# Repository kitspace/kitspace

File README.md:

> ❗ Archived, new development here: [kitspace-v2](https://github.com/kitspace/kitspace-v2)

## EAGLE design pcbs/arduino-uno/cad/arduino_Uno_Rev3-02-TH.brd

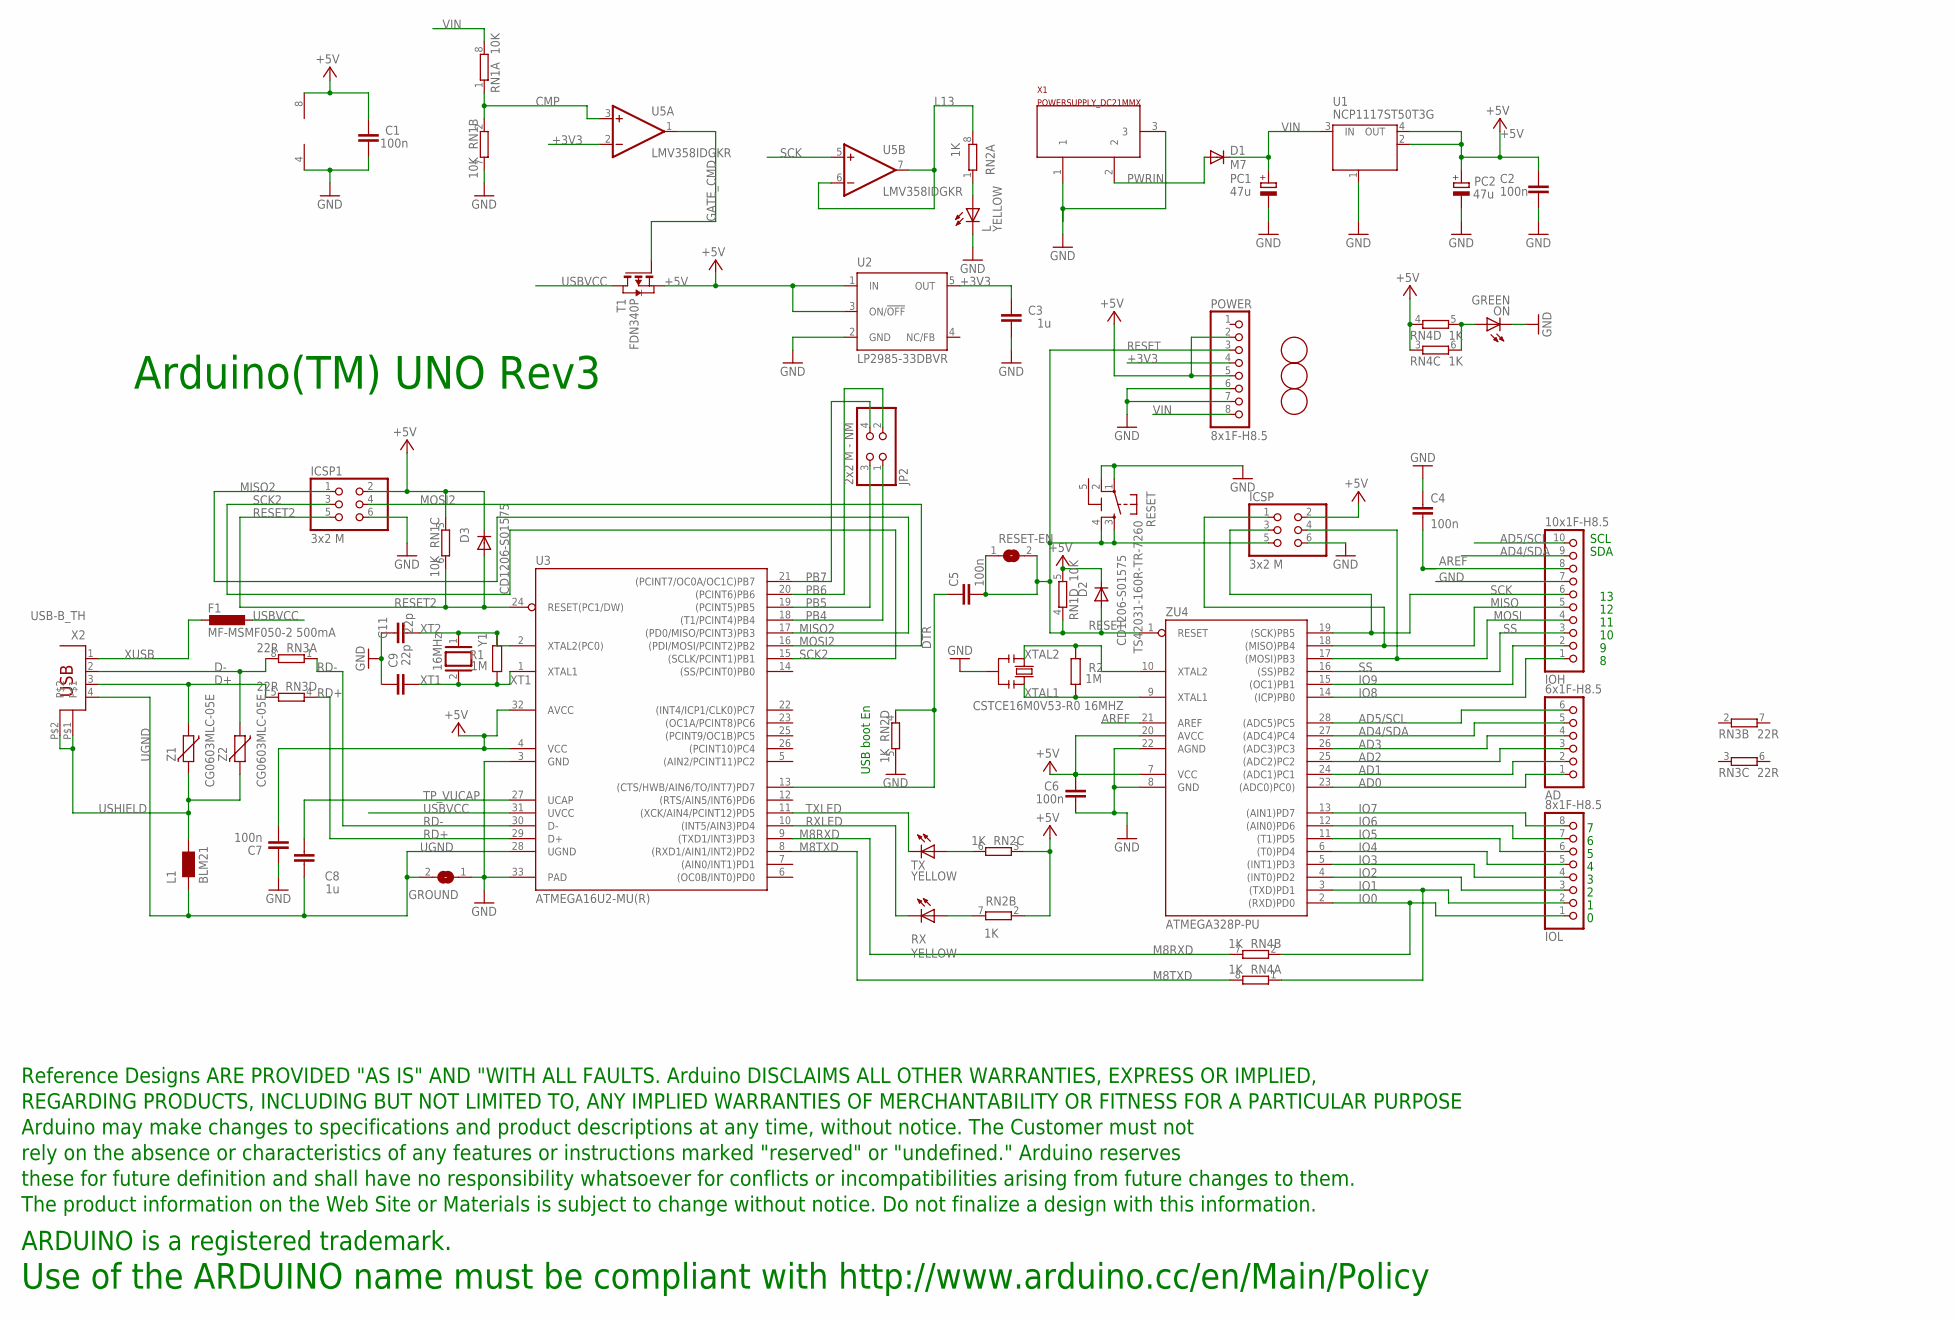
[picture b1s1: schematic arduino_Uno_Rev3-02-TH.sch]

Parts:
AD: 6x1F-H8.5; 1X06
C1, C2, C4, C5, C6, C7: 100n; C0603-ROUND
C3, C8: 1u; C0603-ROUND
C9, C11: 22p; C0603-ROUND
D1: M7; SMB
D2, D3: CD1206-S01575; MINIMELF
F1: MF-MSMF050-2 500mA; L1812
FD1, FD2, FD3: FIDUCIALMOUNT; FIDUCIA-MOUNT
GROUND: SJ
ICSP, ICSP1: 3x2 M; 2X03
IOH: 10x1F-H8.5; 1X10
IOL: 8x1F-H8.5; 1X08
JP2: 2x2 M - NM; 2X02
L: YELLOW; CHIP-LED0805
L1: BLM21; 0805
ON: GREEN; CHIP-LED0805
PC1, PC2: 47u; PANASONIC_D
POWER: 8x1F-H8.5; 1X08
R1, R2: 1M; R0603-ROUND
RESET: TS42031-160R-TR-7260; TS42
RESET-EN: SJ
RN1: 10K; CAY16
RN2, RN4: 1K; CAY16
RN3: 22R; CAY16
RX: YELLOW; CHIP-LED0805
T1: FDN340P; SOT-23
TX: YELLOW; CHIP-LED0805
U1: NCP1117ST50T3G; SOT223
U2: LP2985-33DBVR; SOT23-DBV
U3: ATMEGA16U2-MU(R); MLF32
U5: LMV358IDGKR; MSOP08
U$1: DISCLAIMER
X1: POWERSUPPLY_DC21MMX; POWERSUPPLY_DC-21MM
X2: USB-B_TH; PN61729
Y1: 16MHz; QS
Y2: CSTCE16M0V53-R0 16MHZ; RESONATOR
Z1, Z2: CG0603MLC-05E; CT/CN0603
ZU4: ATMEGA328P-PU; DIL28-3

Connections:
5-GND: RESET.5 (5-GND)
+3V3: C3.2, POWER.4, U2.5 (OUT), U5.2 (-IN)
+5V: C1.2, C2.2, C6.2, C7.1, D2.C, D3.C, ICSP.2, ICSP1.2, PC2.+, POWER.2, POWER.5, RN1.3 (1), RN1.5 (2), RN2.2 (1), RN2.3 (1), RN4.3 (1), RN4.4 (1), T1.2 (S), U1.2 (OUT), U1.4 (OUT), U2.1 (IN), U2.3 (ON/!OFF), U3.4 (VCC), U3.32 (AVCC), U5.8 (V+), ZU4.7 (VCC), ZU4.20 (AVCC)
AD0: AD.1, ZU4.23 ((ADC0)PC0))
AD1: AD.2, ZU4.24 ((ADC1)PC1)
AD2: AD.3, ZU4.25 ((ADC2)PC2)
AD3: AD.4, ZU4.26 ((ADC3)PC3)
AD4/SDA: AD.5, IOH.9, ZU4.27 ((ADC4)PC4)
AD5/SCL: AD.6, IOH.10, ZU4.28 ((ADC5)PC5)
AREF: C4.2, IOH.8, ZU4.21 (AREF)
CMP: RN1.1, RN1.2 (1), U5.3 (+IN)
D+: RN3.5 (2), X2.3, Z1.1
D-: RN3.8 (2), X2.2, Z2.1
DTR: C5.1, RN2.4 (1), U3.13 ((CTS/HWB/AIN6/TO/INT7)PD7)
GATE_CMD: T1.3 (G), U5.1 (OUT)
GND: C1.1, C2.1, C3.1, C4.1, C6.1, C7.2, C9.2, C11.2, GROUND.1, ICSP.6, ICSP1.6, IOH.7, L.C, ON.C, PC1.-, PC2.-, POWER.6, POWER.7, RESET.1, RESET.2, RN1.7 (2), RN2.5 (2), U1.1 (GND/ADJ), U2.2 (GND), U3.3 (GND), U3.33 (PAD), U5.4 (V-), X1.1, X1.3, Y2.2, ZU4.8 (GND), ZU4.22 (AGND)
IO0: IOL.1, RN4.2 (1), ZU4.2 ((RXD)PD0)
IO1: IOL.2, RN4.1, ZU4.3 ((TXD)PD1)
IO2: IOL.3, ZU4.4 ((INT0)PD2)
IO3: IOL.4, ZU4.5 ((INT1)PD3)
IO4: IOL.5, ZU4.6 ((T0)PD4)
IO5: IOL.6, ZU4.11 ((T1)PD5)
IO6: IOL.7, ZU4.12 ((AIN0)PD6)
IO7: IOL.8, ZU4.13 ((AIN1)PD7)
IO8: IOH.1, ZU4.14 ((ICP)PB0)
IO9: IOH.2, ZU4.15 ((OC1)PB1)
L13: RN2.8 (2), U5.6 (-IN), U5.7 (OUT)
M8RXD: RN4.7 (2), U3.9 ((TXD1/INT3)PD3)
M8TXD: RN4.8 (2), U3.8 ((RXD1/AIN1/INT2)PD2)
MISO: ICSP.1, IOH.5, ZU4.18 ((MISO)PB4)
MISO2: ICSP1.1, U3.17 ((PD0/MISO/PCINT3)PB3)
MOSI: ICSP.4, IOH.4, ZU4.17 ((MOSI)PB3)
MOSI2: ICSP1.4, U3.16 ((PDI/MOSI/PCINT2)PB2)
unnamed: L.A, RN2.1
unnamed: ON.A, RN4.5 (2), RN4.6 (2)
unnamed: RN2.7 (2), RX.A
unnamed: RN2.6 (2), TX.A
PB4: JP2.1, U3.18 ((T1/PCINT4)PB4)
PB5: JP2.3, U3.19 ((PCINT5)PB5)
PB6: JP2.2, U3.20 ((PCINT6)PB6)
PB7: JP2.4, U3.21 ((PCINT7/OC0A/OC1C)PB7)
PWRIN: D1.A, X1.2
RD+: RN3.4 (1), U3.29 (D+)
RD-: RN3.1, U3.30 (D-)
RESET: C5.2, D2.A, ICSP.5, POWER.3, RESET.3, RESET.4, RESET-EN.1, RESET-EN.2, RN1.4 (1), ZU4.1 (RESET)
RESET2: D3.A, ICSP1.5, RN1.6 (2), U3.24 (RESET(PC1/DW))
RXLED: RX.C, U3.10 ((INT5/AIN3)PD4)
SCK: ICSP.3, IOH.6, U5.5 (+IN), ZU4.19 ((SCK)PB5)
SCK2: ICSP1.3, U3.15 ((SCLK/PCINT1)PB1)
SS: IOH.3, ZU4.16 ((SS)PB2)
TP_VUCAP: C8.1, U3.27 (UCAP)
TXLED: TX.C, U3.11 ((XCK/AIN4/PCINT12)PD5)
UGND: C8.2, GROUND.2, L1.1, U3.28 (UGND), X2.4
USBVCC: F1.1, T1.1 (D), U3.31 (UVCC)
USHIELD: L1.2, X2.P$1, X2.P$2, Z1.2, Z2.2
VIN: D1.C, PC1.+, POWER.8, RN1.8 (2), U1.3 (IN)
XT1: C9.1, R1.1, U3.1 (XTAL1), Y1.2
XT2: C11.1, R1.2, U3.2 (XTAL2(PC0)), Y1.1
XTAL1: R2.1, Y2.3, ZU4.9 (XTAL1)
XTAL2: R2.2, Y2.1, ZU4.10 (XTAL2)
XUSB: F1.2, X2.1

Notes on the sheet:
Arduino(TM) UNO Rev3
USB boot En
SDA
SCL
Use of the ARDUINO name must be compliant with http://www.arduino.cc/en/Main/Policy

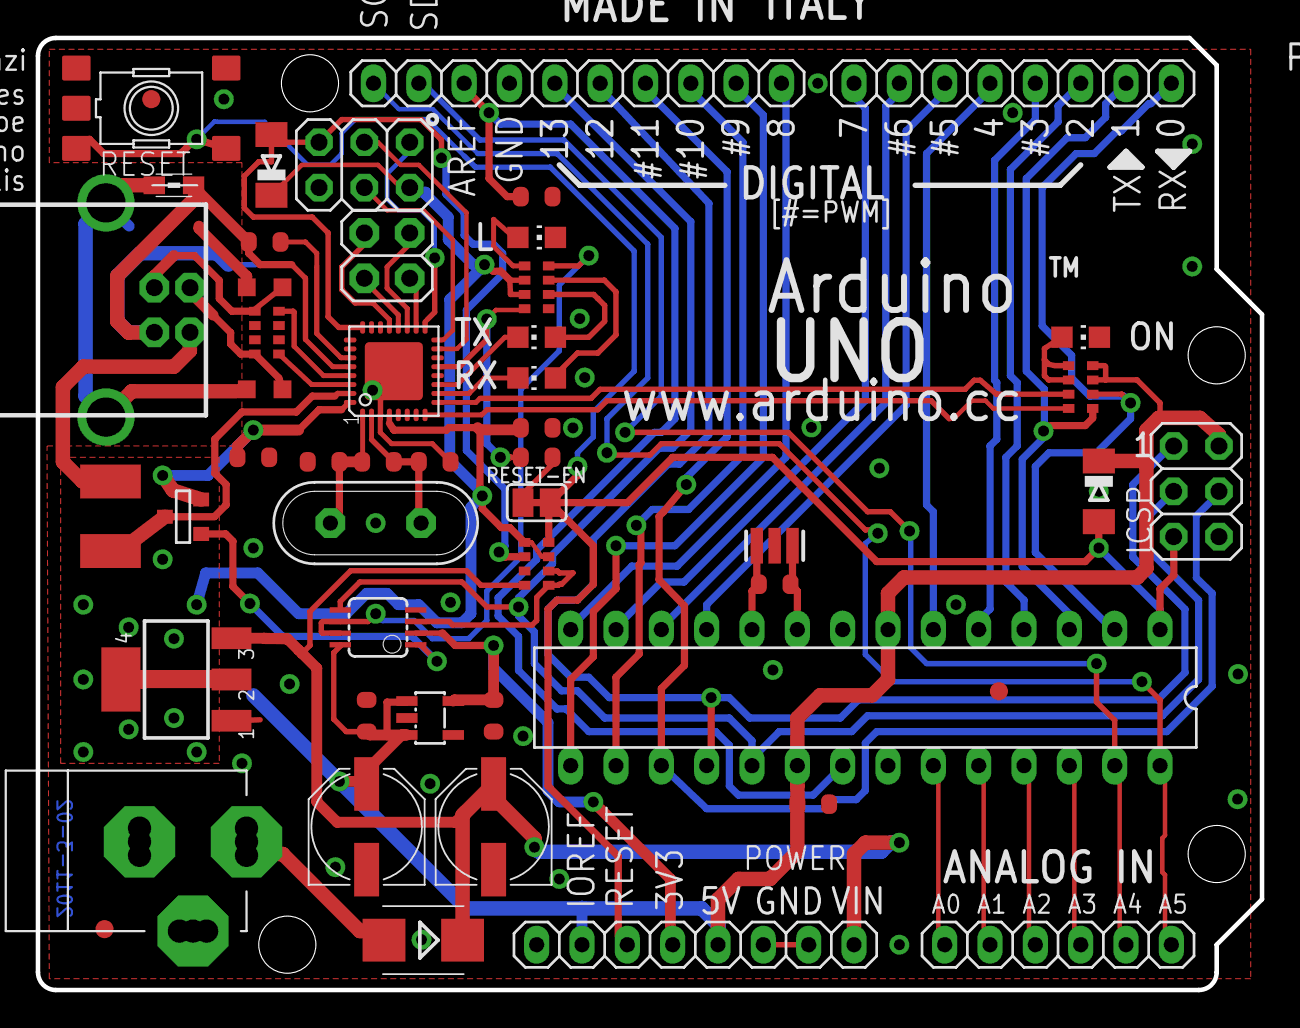
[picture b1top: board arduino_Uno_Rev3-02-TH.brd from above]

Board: 2 copper layers, 68.6 x 53.3 mm, 53 parts (1 on the bottom side), 60 nets.

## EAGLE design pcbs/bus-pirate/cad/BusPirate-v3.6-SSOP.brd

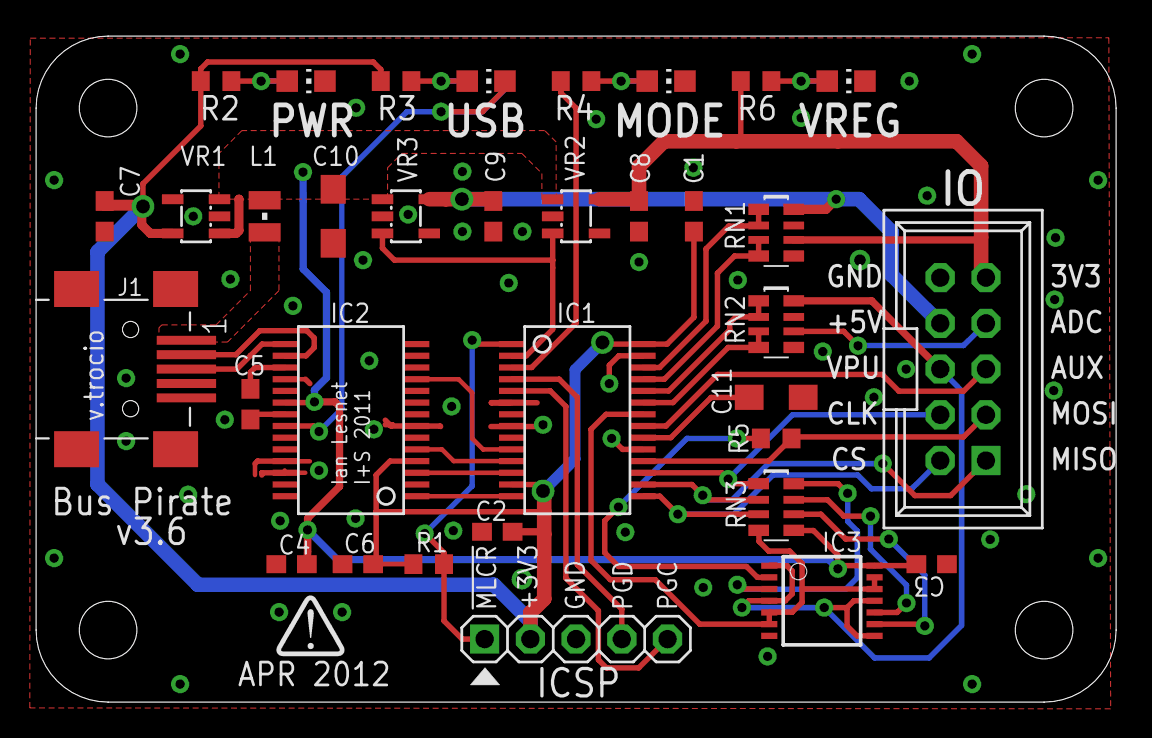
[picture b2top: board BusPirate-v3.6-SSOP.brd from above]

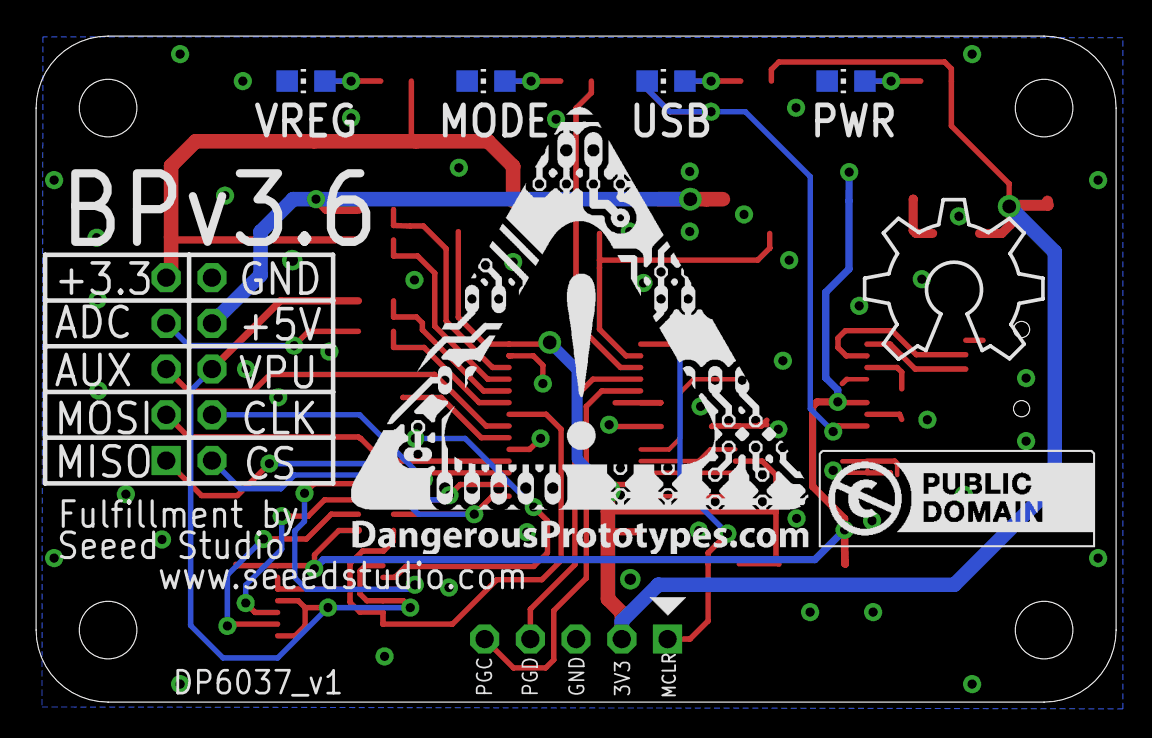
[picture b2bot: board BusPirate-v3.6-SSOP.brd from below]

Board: 2 copper layers, 60.0 x 37.0 mm, 43 parts (7 on the bottom side), 40 nets.

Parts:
C1, C2, C3, C4, C5, C6: 0.1uF; C603
C7, C8, C9: 1uF; C603
C10, C11: 10uF; SMC_A
IC1: PIC24FJ64GA002; SSOP28
IC2: FT232RL; SSOP28
IC3: 4066; TSSOP14
ICSP: 1X05
IO: HEADER2X5-SHRD-PTH-B; PINSHRD_PTH_2X05B
J1: CON-USB-MINI-BUSB1; CONN_USB_MINI-B
L1: 700mA+ ferrite; WE-KI_0805_B
LED1, LED1A, LED2, LED2A, LED3, LED3A, LED4, LED4A: CHIP-LED0805
LOGO1: LOGO_CC-0
PCB1: PCB_DP_RECTANGLE-37X60; DP6037_V1
R1, R5: 2K; R603
R2, R3, R4, R6: 1K1; R603
RN1, RN2, RN3: 10k; RN8P-4R-CRA06S
U$1: DP-LOGO
U$2: OSHW_8X350_NOTEXT
U$3: DP_LOGO_ART_1X1
VR1, VR2: MCP1801T-3302I/OT; SOT-23-5
VR3: MCP1801T-5002I/OT; SOT-23-5

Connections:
$N26: J1.VUSB, L1.2
ADC: IO.7, RN2.6
ADC1: IC1.23, RN2.3, RN2.4
ADC2: IC1.24, RN2.1, RN2.2
ADC3: IC1.25, RN1.3, RN1.4
ADC4: IC1.26, RN1.1, RN1.2
AUX1: IC1.21, IO.5
CLK: IC1.17, IO.4, RN3.1
CS: IC1.15, IO.2, RN3.3
CTS: IC1.10, IC2.11
GND: C1.2, C2.2, C3.2, C4.2, C5.2, C6.2, C7.2, C8.2, C9.2, C10.-, C11.-, IC1.6, IC1.7, IC1.8, IC1.19, IC1.27, IC2.7, IC2.18, IC2.21, IC2.25, IC2.26, IC3.7, ICSP.3, IO.10, J1.GND, LED1.C, LED1A.C, LED2.C, LED2A.C, LED3.C, LED3A.C, RN1.5, RN1.7, RN2.5, RN2.7, VR1.2, VR2.2, VR3.2
LD1: IC1.3, R4.2
MCLR: IC1.1, ICSP.1, R1.1
MISO: IC1.16, IO.1, RN3.2
MOSI: IC1.18, IO.3, R5.1
unnamed: IC3.2, R5.2
unnamed: IC3.9, RN3.6
unnamed: C11.+, IC1.20
unnamed: IC3.10, RN3.7
unnamed: IC3.3, RN3.8
unnamed: LED2.A, LED2A.A, R4.1
unnamed: LED1.A, LED1A.A, R2.1
unnamed: C5.1, IC2.17
unnamed: LED4.A, LED4A.A, R3.1
unnamed: IC2.15, J1.D+
unnamed: IC2.16, J1.D-
unnamed: LED3.A, LED3A.A, R6.1
PGC: IC1.5, ICSP.5
PGD: IC1.4, ICSP.4
PULLUPEN: IC1.22, IC3.5, IC3.6, IC3.12, IC3.13, RN3.4
RTS: IC1.12, IC2.3
RX: IC1.11, IC2.5
RXLED: IC2.22, LED4.C, LED4A.C
SWV33: C8.1, IO.9, R6.2, RN1.6, VR2.5
SWV50: C9.1, IO.8, RN1.8, VR3.5
TX: IC1.14, IC2.1
V+: C3.1, C4.1, C10.+, IC2.20, IC3.14, L1.1, RN3.5, VR1.1, VR1.3, VR2.1, VR3.1
VCC: C1.1, C2.1, C6.1, C7.1, IC1.13, IC1.28, IC2.4, ICSP.2, R1.2, R2.2, R3.2, VR1.5
VEXTERN: IC3.1, IC3.4, IC3.8, IC3.11, IO.6, RN2.8
VREGEN: IC1.2, VR2.3, VR3.3

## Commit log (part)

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2021-03-04 Add re-direct for turn signal
2021-03-09 Bump elliptic from 6.5.2 to 6.5.4
    Bumps [elliptic](https://github.com/indutny/elliptic) from 6.5.2 to 6.5.4.
    - [Release notes](https://github.com/indutny/elliptic/releases)
    - [Commits](https://github.com/indutny/elliptic/compare/v6.5.2...v6.5.4)
2021-03-10 Add odour stimulator board (#322)
2021-03-11 Upgrade tracespace tools to ^4.2
2021-03-11 Work around updated whats-that-gerber matching more files
2021-03-12 Make /submit work with updated tracespace
2021-03-12 Add global plausible for custom events
2021-03-12 Add plausible events for extension install
2021-03-12 Omit ibom for maulwurf
2021-03-13 Try aux click handler for aisler
2021-03-15 Remove check for plausible function
2021-03-17 Simplify order PCB tracking
2021-03-17 Add s to Order PCBs event
2021-03-18 Add tinyogx project
2021-03-22 Add openflexure-constant-current-illumination
2021-03-24 Remove smoke test
2021-03-30 Bump y18n from 3.2.1 to 3.2.2
    Bumps [y18n](https://github.com/yargs/y18n) from 3.2.1 to 3.2.2.
    - [Release notes](https://github.com/yargs/y18n/releases)
    - [Changelog](https://github.com/yargs/y18n/blob/master/CHANGELOG.md)
    - [Commits](https://github.com/yargs/y18n/commits)
2021-04-14 Add boards from the beehive project (#329)
2021-04-18 feat: Updates board URL to source repository
    Pull request to merge kitspace code has been merged see https://github.com/drspangle/infidel-sensor/pull/23
2021-04-19 Change beehive url to beehive-org
2021-04-22 Make sure kicad plotting folders for multi are seperate
2021-04-25 Bump ini from 1.3.5 to 1.3.8 (#325)
    Bumps [ini](https://github.com/isaacs/ini) from 1.3.5 to 1.3.8.
    - [Release notes](https://github.com/isaacs/ini/releases)
    - [Commits](https://github.com/isaacs/ini/compare/v1.3.5...v1.3.8)
2021-04-26 Bump http-proxy from 1.18.0 to 1.18.1 (#303)
    Bumps [http-proxy](https://github.com/http-party/node-http-proxy) from 1.18.0 to 1.18.1.
    - [Release notes](https://github.com/http-party/node-http-proxy/releases)
    - [Changelog](https://github.com/http-party/node-http-proxy/blob/master/CHANGELOG.md)
    - [Commits](https://github.com/http-party/node-http-proxy/compare/1.18.0...1.18.1)
2021-05-01 fix: Corrects repo typo
2021-05-05 Added 3 Channel Diversity System Controller (#335)
2021-05-06 Bump ua-parser-js from 0.7.21 to 0.7.28
    Bumps [ua-parser-js](https://github.com/faisalman/ua-parser-js) from 0.7.21 to 0.7.28.
    - [Release notes](https://github.com/faisalman/ua-parser-js/releases)
    - [Commits](https://github.com/faisalman/ua-parser-js/compare/0.7.21...0.7.28)
2021-05-10 Bump hosted-git-info from 2.8.5 to 2.8.9
    Bumps [hosted-git-info](https://github.com/npm/hosted-git-info) from 2.8.5 to 2.8.9.
    - [Release notes](https://github.com/npm/hosted-git-info/releases)
    - [Changelog](https://github.com/npm/hosted-git-info/blob/v2.8.9/CHANGELOG.md)
    - [Commits](https://github.com/npm/hosted-git-info/compare/v2.8.5...v2.8.9)
2021-05-12 Update boards.txt
    Add GPSMux board
2021-05-13 Test Driverino Shield
2021-05-13 Just deploy it
2021-06-10 Run yarn upgrade
2021-06-19 Upgrade netlify-cli, make use of prodIfUnlocked flag
2021-06-19 Add bomanz to omit-ibom
2021-06-20 Work around htmltojsx bug in makeReadme
2021-06-20 Add nasa-jpl/open-source-rover
2021-06-20 Revert "Simplify git cloning process"
    This reverts commit 1f51ce97e80735f7355dbb5525eaeb893e6f500b.
2021-06-20 Try miriam
2021-06-21 Add explicit dep on IBOM.jsx
2021-06-21 Add env vars to github action
2021-06-21 Revert "Stop recording in smoke-test"
    This reverts commit 2b794929cbc1d2cab8aa8b44c51897e9b5f9f131.
2021-06-21 Try basic github action
2021-06-21 Add setup in github action
2021-06-21 Add build step
2021-06-21 Add xvfb to github action
2021-06-21 Try IBOM without X
2021-06-21 Switch InteractiveHtmlBom to kitspace-config-2 branch
2021-06-21 Try using CYPRESS_RECORD_KEY var
2021-06-21 Try deploy using github action
2021-06-21 Remove all travis ci related stuff
2021-06-24 Remove footprints to modules rename for ibom
2021-06-24 Pass on GH_TOKEN to build CI job
2021-06-24 Add Tyler-Ward/stacklight-hardware
2021-06-24 Add gregdavill/d20-hardware
2021-06-25 Add hutscape/oak
2021-06-25 Revert "Add hutscape/oak (#348)"
    This reverts commit 6c3f68caabb1a7c4602ff4b54afc50aa09f63569.
2021-06-25 Try both
2021-06-26 Update 1-click-bom for quantity inference and better tab handling
2021-06-26 Update npm-1-click-bom for better mouser URL parsing
2021-06-28 Add dhairyashah1/USBee32-S2
2021-06-28 Uninstall git lfs before doing get_boards
2021-06-29 Try rigol-DP832-USB-C-adapter
2021-06-30 Try satellite_tracker
2021-07-08 Try hydromisc
2021-07-11 Fix trailing slash on pslab in registry.json
2021-07-11 Try and fix unshallow
2021-07-11 Fix missing && in get_boards
2021-07-12 Work around issue with pslab-hardware shallow clone
2021-07-13 Try parasite
2021-07-14 Update npm-1-click-bom for better header finding
2021-07-15 Update npm-1-click-bom for pcs/pcb alias
2021-07-15 Lock USBee32-S2 to working version
2021-07-16 Try watchy
2021-07-20 Add test_tube_photometer
2021-07-20 Add OtterCastAudioV2
2021-07-20 Add OtterCastAmp (#353)
2021-07-22 Add LibreSolar/mppt-1210-hus
2021-07-23 Add task for remote processing of kicad to layout.svg
2021-07-23 Check for processor failure in makeLayoutSvg.js
2021-08-11 Bump path-parse from 1.0.6 to 1.0.7
    Bumps [path-parse](https://github.com/jbgutierrez/path-parse) from 1.0.6 to 1.0.7.
    - [Release notes](https://github.com/jbgutierrez/path-parse/releases)
    - [Commits](https://github.com/jbgutierrez/path-parse/commits/v1.0.7)
    ---
    updated-dependencies:
    - dependency-name: path-parse
2021-08-20 Remove JLC Assembly columns from BOMs
2021-09-07 Add LouisLab/pivr (#363)
2021-10-07 Correct capitalisation in _redirects
2021-10-08 Add docs about new "pcb-services" field in yaml
2021-10-10 Disable "buy parts" when no parts specified
2021-10-10 Disable "buy parts" when no parts specified (#365)
2021-10-28 Add DropBot test board
2021-11-05 Add DropBot switching board
2021-11-08 Try dropbot 40 channel switching board
2021-11-10 Add dropbot-boards
2021-11-15 Adding ulx4m board
2021-11-16 Bump aws-sdk from 2.658.0 to 2.1030.0
    Bumps [aws-sdk](https://github.com/aws/aws-sdk-js) from 2.658.0 to 2.1030.0.
    - [Release notes](https://github.com/aws/aws-sdk-js/releases)
    - [Changelog](https://github.com/aws/aws-sdk-js/blob/master/CHANGELOG.md)
    - [Commits](https://github.com/aws/aws-sdk-js/compare/v2.658.0...v2.1030.0)
    ---
    updated-dependencies:
2021-11-24 Try Xassette-Asterisk
2021-11-25 Add Xassette-Asterisk (#372)
2021-12-02 Bump jszip from 3.2.2 to 3.7.0
    Bumps [jszip](https://github.com/Stuk/jszip) from 3.2.2 to 3.7.0.
    - [Release notes](https://github.com/Stuk/jszip/releases)
    - [Changelog](https://github.com/Stuk/jszip/blob/master/CHANGES.md)
    - [Commits](https://github.com/Stuk/jszip/compare/v3.2.2...v3.7.0)
    ---
    updated-dependencies:
2022-01-13 Update boards.txt
    add fedwatcher RPi shield
2022-01-13 Add pyphotometry board (#377)
2022-01-19 Temporarily lock-down hoverboard-breakout to working version
2022-02-24 Try air-quality-monitor
2022-02-24 Update kicad to version 6
2022-03-09 Try XboxHDMI
2022-03-10 Fix get_boards
2022-03-15 Bump lodash-es from 4.17.15 to 4.17.21
    Bumps [lodash-es](https://github.com/lodash/lodash) from 4.17.15 to 4.17.21.
    - [Release notes](https://github.com/lodash/lodash/releases)
    - [Commits](https://github.com/lodash/lodash/compare/4.17.15...4.17.21)
    ---
    updated-dependencies:
    - dependency-name: lodash-es
2022-04-01 Temporarily lock down OtterCastV2 to working version
2022-05-16 Bump nanoid from 3.1.23 to 3.3.4
    Bumps [nanoid](https://github.com/ai/nanoid) from 3.1.23 to 3.3.4.
    - [Release notes](https://github.com/ai/nanoid/releases)
    - [Changelog](https://github.com/ai/nanoid/blob/main/CHANGELOG.md)
    - [Commits](https://github.com/ai/nanoid/compare/3.1.23...3.3.4)
    ---
    updated-dependencies:
2022-06-23 Bump jsdom from 9.12.0 to 16.5.0
    Bumps [jsdom](https://github.com/jsdom/jsdom) from 9.12.0 to 16.5.0.
    - [Release notes](https://github.com/jsdom/jsdom/releases)
    - [Changelog](https://github.com/jsdom/jsdom/blob/master/Changelog.md)
    - [Commits](https://github.com/jsdom/jsdom/compare/9.12.0...16.5.0)
    ---
    updated-dependencies:
2022-06-23 Update jsdom to 20
2022-06-28 Adding balthazar-space keyboard (#387)
2022-06-29 One more board from balthazar-space (#388)
2022-06-29 Upgrade to kicad 6
2022-06-29 Hack for ibom config
2022-06-29 Revert "One more board from balthazar-space (#388)"
    This reverts commit f111a90ce9a32853e59d0c420332aa9e1a4c1be6.
2022-06-29 Adding Unifying board (#389)
2022-07-03 Add Open-Gamma-Detector (#391)
2022-07-08 Bump moment from 2.27.0 to 2.29.4
    Bumps [moment](https://github.com/moment/moment) from 2.27.0 to 2.29.4.
    - [Release notes](https://github.com/moment/moment/releases)
    - [Changelog](https://github.com/moment/moment/blob/develop/CHANGELOG.md)
    - [Commits](https://github.com/moment/moment/compare/2.27.0...2.29.4)
    ---
    updated-dependencies:
2022-07-13 Remove test
2022-07-14 Add key-ripper
    https://github.com/bschwind/key-ripper/pull/13
2022-07-15 Try 4chord-midi
2022-07-20 Fix isssue with finding .kicad_pcb
2022-07-28 Add threeboard
    https://github.com/taylorconor/threeboard/pull/9
2022-09-20 Try micro-bot on its own
2022-09-20 Update boards.txt
    Added four Rosmo.io boards
2022-09-28 Revert "Temporarily remove diplexer"
    This reverts commit 248b8678cd7bbb9ea7cfa7f704172fa42ca547c5.
2022-09-30 Update _redirects
2022-10-01 Temporarily remove piezo-sensor
2022-10-02 Add diplexer and 8bitmixtape to omit ibom
2022-10-02 Try default kicad on ubuntu 22.04
2022-10-02 Revert "Temporarily remove piezo-sensor"
    This reverts commit 31f23a8333b428d7a1ec631651fee4355b889e40.
2022-10-03 Try updated nunchuk
2022-10-05 Add spikeling v2.0 (#400)
2022-11-15 [ImgBot] Optimize images
    *Total -- 413.61kb -> 322.15kb (22.11%)
    /image_src/submit.svg -- 2.60kb -> 0.94kb (64.05%)
    /docs/planned.png -- 41.96kb -> 15.79kb (62.37%)
    /docs/current.png -- 26.25kb -> 11.59kb (55.84%)
    /src/images/logo.png -- 12.94kb -> 6.34kb (51%)
    /src/images/mag_icon.svg -- 3.06kb -> 1.50kb (50.78%)
2022-11-16 Increase outline gap fill to 9mm
2022-12-01 Add redirect for BeeHive/boards
2022-12-02 add rrf_rpi_skr_adapter (#401)
2022-12-04 Add ArdPromSD (#405)
2023-01-06 Bump json5 from 2.1.3 to 2.2.3
    Bumps [json5](https://github.com/json5/json5) from 2.1.3 to 2.2.3.
    - [Release notes](https://github.com/json5/json5/releases)
    - [Changelog](https://github.com/json5/json5/blob/main/CHANGELOG.md)
    - [Commits](https://github.com/json5/json5/compare/v2.1.3...v2.2.3)
    ---
    updated-dependencies:
2023-01-09 Update breakpoint for more pcb services
2023-01-16 Add redirects for OpenGammaProject rename
2023-01-16 Try breadboard-io
2023-01-16 Update npm-1-click-bom
2023-01-23 Bump cookiejar from 2.1.2 to 2.1.4
    Bumps [cookiejar](https://github.com/bmeck/node-cookiejar) from 2.1.2 to 2.1.4.
    - [Release notes](https://github.com/bmeck/node-cookiejar/releases)
    - [Commits](https://github.com/bmeck/node-cookiejar/commits)
    ---
    updated-dependencies:
    - dependency-name: cookiejar
2023-01-31 Lock down key-ripper
2023-01-31 Re-direct key-ripper to multi project
2023-02-01 Use repoPath for readme pattern
2023-02-02 Bump jszip from 3.2.2 to 3.8.0
    Bumps [jszip](https://github.com/Stuk/jszip) from 3.2.2 to 3.8.0.
    - [Release notes](https://github.com/Stuk/jszip/releases)
    - [Changelog](https://github.com/Stuk/jszip/blob/main/CHANGES.md)
    - [Commits](https://github.com/Stuk/jszip/compare/v3.2.2...v3.8.0)
    ---
    updated-dependencies:
2023-02-11 Revert "Temp change add-a-project link to readme"
    This reverts commit 163f92471d41c21dfbb9c52c33510b4cfa23ff2c.
2023-02-11 Remove links to /submit
2023-02-14 Try mlab USBI2C01
2023-02-15 Adding MLAB USBI2C01 (#413)
2023-02-19 Test node version
2023-02-19 Try kicad 7
2023-04-06 Disable running github action on cron schedule
2023-04-15 Lock down ruler to kicad 6 version
2023-04-15 Add MicroFC-SiPM-Array-Board (#414)
2023-05-17 Add favicons in many more sizes
2023-05-30 Add more favicons
2023-06-13 Add Tiny-MicroFC-Carrier-Board (#415)
2023-11-12 Revert "Allow triggering via workflow dispatch"
    This reverts commit 6cec54e4d87b6ea541cc9c68905a9ef7b44c00d8.
2024-04-27 Add hawk (#417)
